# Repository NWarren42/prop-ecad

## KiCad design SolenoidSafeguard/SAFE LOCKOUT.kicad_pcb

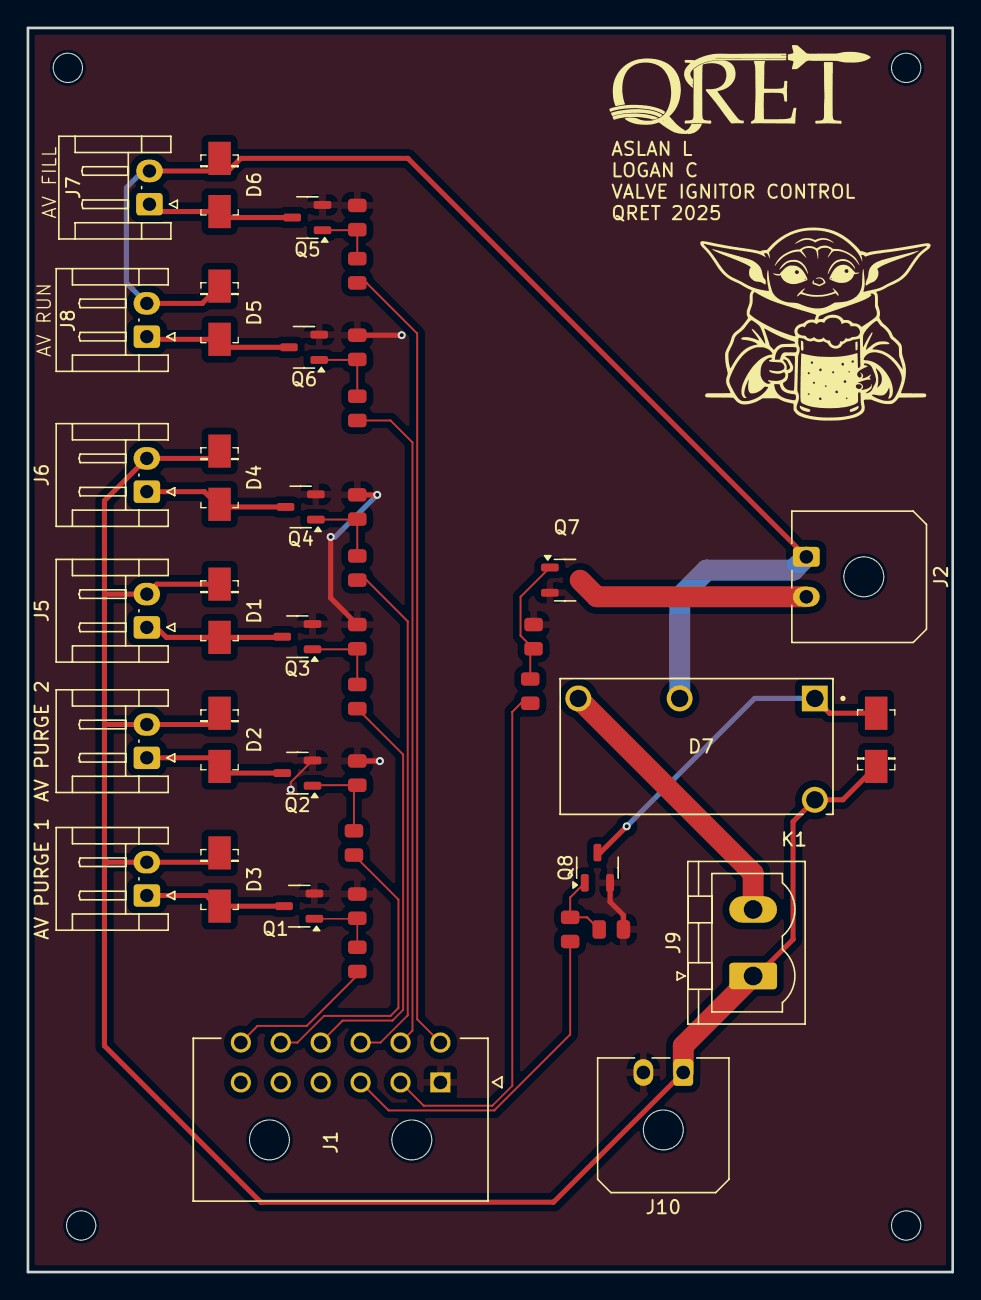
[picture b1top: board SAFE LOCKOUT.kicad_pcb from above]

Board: 2 copper layers, 69.5 x 93.5 mm, 42 parts (0 on the bottom side), 28 nets.

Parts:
AV PURGE 1, AV PURGE 2: Conn_01x02_Pin; JST_EH_S2B-EH_1x02_P2.50mm_Horizontal
D1, D2, D3, D4, D5, D6, D7: S1G; DO-214AC
J1: Conn_01x12_Pin; MOLEX_430451200
J2, J10: Conn_01x02_Pin; Molex_Micro-Fit_3.0_43650-0200_1x02_P3.00mm_Horizontal
J5, J6, J7, J8: Conn_01x02_Pin; JST_EH_S2B-EH_1x02_P2.50mm_Horizontal
J9: Conn_01x02_Pin; PhoenixContact_MSTBVA_2,5_2-G_1x02_P5.00mm_Vertical
K1: PR30-24V-450-1A; RELAY_PR30-24V-450-1A
Q1, Q2, Q3, Q4, Q5, Q6, Q7, Q8: BSS138; SOT-23-3
R1, R3, R5, R7, R9, R11, R13, R15: R100; R_0805
R2, R4, R6, R8, R10, R12, R16: 100KR; R_0805
R14: R100K; R_0805

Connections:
+24V: AV PURGE 1.2, AV PURGE 2.2, D1.K, D2.K, D3.K, D4.K, D7.K, J5.2, J6.2, J9.1, J10.1, K1.16
AV RUN CTL: J1.8, R11.1
AV FILL CTL: J1.7, R9.1
AV FILL VLV: D6.A, J7.1, Q5.3 (D)
AV RUN VLV: D5.A, J8.1, Q6.3 (D)
GND: J1.1, J10.2, Q1.2 (S), Q2.2 (S), Q3.2 (S), Q4.2 (S), Q5.2 (S), Q6.2 (S), Q7.2 (S), Q8.2 (S), R2.1, R4.1, R6.1, R8.1, R10.1, R12.1, R14.1, R16.1
IGNITOR 3A -: J2.2, Q7.3 (D)
IGNITOR CTL: J1.2, R13.1
unnamed: J9.2, K1.8
unnamed: Q1.1 (G), R1.2, R2.2
unnamed: Q2.1 (G), R3.2, R4.2
unnamed: Q3.1 (G), R5.2, R6.2
unnamed: Q4.1 (G), R7.2, R8.2
unnamed: Q5.1 (G), R9.2, R10.2
unnamed: Q6.1 (G), R11.2, R12.2
unnamed: Q7.1 (G), R13.2, R14.2
unnamed: D7.A, K1.1, Q8.3 (D)
unnamed: Q8.1 (G), R15.2, R16.2
RELAY SFEGRD CTL: J1.3, R15.1
SAFE POWER 24v: D5.K, D6.K, J2.1, J7.2, J8.2, K1.5
VLV 1: AV PURGE 1.1, D3.A, Q1.3 (D)
VLV 1 CTL: J1.12, R1.1
VLV 2: AV PURGE 2.1, D2.A, Q2.3 (D)
VLV 2 CTL: J1.11, R3.1
VLV 3: D1.A, J5.1, Q3.3 (D)
VLV 3 CTL: J1.10, R5.1
VLV 4: D4.A, J6.1, Q4.3 (D)
VLV 4 CTL: J1.9, R7.1

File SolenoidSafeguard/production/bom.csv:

Designator,Footprint,Quantity,Value,LCSC Part #
"D1, D2, D3, D4, D5, D6, D7",DO-214AC,7,S1G,S1G
J1,MOLEX_430451200,1,Conn_01x12_Pin,
"J10, J2",Molex_Micro-Fit_3.0_43650-0200_1x02_P3.00mm_Horizontal,2,Conn_01x02_Pin,
"J3, J4, J5, J6, J7, J8",JST_EH_S2B-EH_1x02_P2.50mm_Horizontal,6,Conn_01x02_Pin,
J9,"PhoenixContact_MSTBVA_2,5_2-G_1x02_P5.00mm_Vertical",1,Conn_01x02_Pin,
K1,RELAY_PR30-24V-450-1A,1,PR30-24V-450-1A,
"Q1, Q2, Q3, Q4, Q5, Q6, Q7, Q8",SOT-23-3,8,BSS138,BSS138
"R1, R11, R13, R15, R3, R5, R7, R9",R_0805,8,R100,
"R10, R12, R16, R2, R4, R6, R8",R_0805,7,100KR,
R14,R_0805,1,R100K,

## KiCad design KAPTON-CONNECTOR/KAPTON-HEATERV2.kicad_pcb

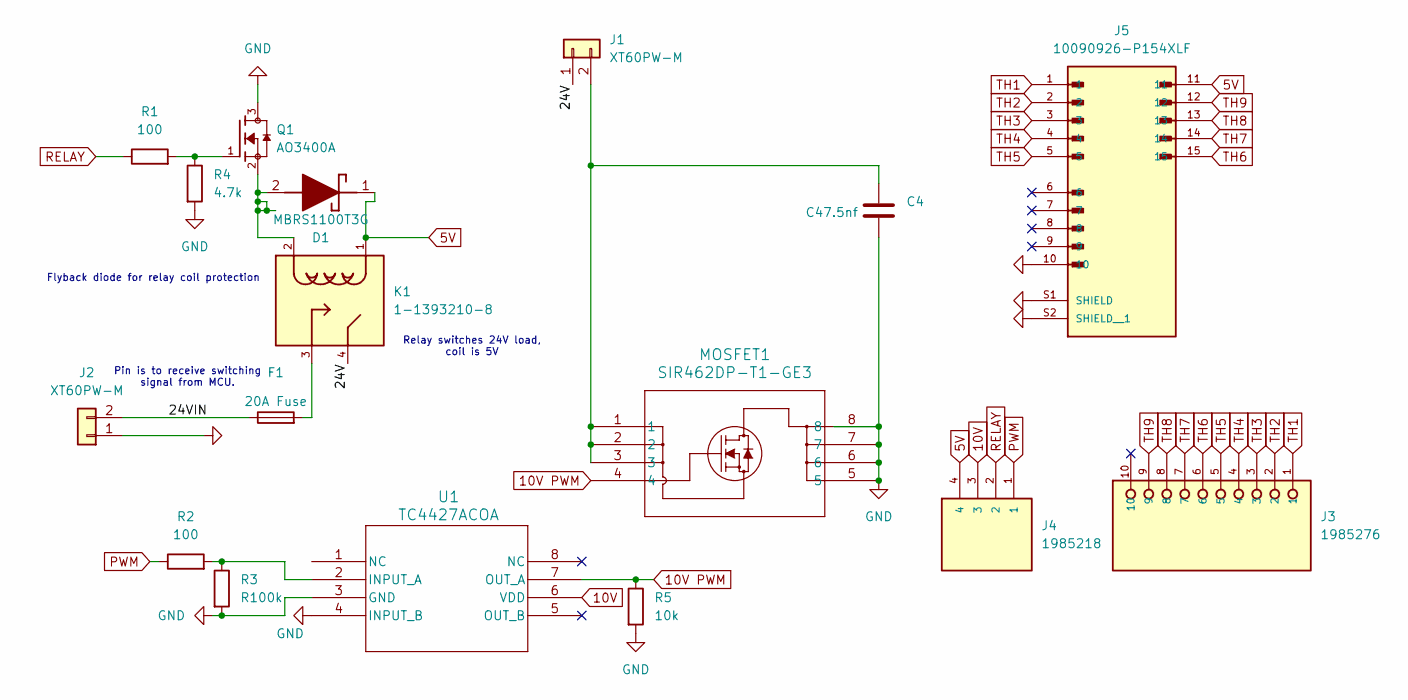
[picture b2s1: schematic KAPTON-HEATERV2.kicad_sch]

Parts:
C4: C47.5nf; C_0805_2012Metric
D1: MBRS1100T3G; DIOM5436X247N; Mouser Part Number 863-MBRS1100T3G
F1: 20A Fuse; FUSRR508W60L835T400H810
J1, J2: XT60PW-M; AMASS_XT60PW-M
J3: 1985276; PHOENIX_1985276
J4: 1985218; TE_1985218; PARTREV 29.03.2021
J5: 10090926-P154XLF; AMPHENOL_10090926-P154XLF; PARTREV H
K1: 1-1393210-8; RELAY_1-1393210-8; PARTREV 0815
MOSFET1: SIR462DP-T1-GE3; POWERPAK_SO-8_SINGLE_VIS
Q1: AO3400A; SOT95P280X125-3N; PARTREV L
R1, R2: 100; R_1206
R3: R100k; R_0805_2012Metric
R4: 4.7k; R_1206
R5: 10k; R_1206
U1: TC4427ACOA; SOIC8-N_MC_MCH

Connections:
5V: D1.1 (K), J4.4, J5.11, K1.1
10V: J4.3, U1.6 (VDD)
10V PWM: MOSFET1.4, R5.1, U1.7 (OUT_A)
/24V: J1.1, K1.4
/24VIN: F1.1, J2.2
GND: C4.1, J2.1, J5.10, J5.S1 (SHIELD), J5.S2 (SHIELD__1), MOSFET1.5, MOSFET1.6, MOSFET1.7, MOSFET1.8, Q1.3, R3.2, R4.2, R5.2, U1.3 (GND), U1.4 (INPUT_B)
unnamed: D1.2 (A), K1.2, Q1.2
unnamed: F1.2, K1.3
unnamed: C4.2, J1.2, MOSFET1.1, MOSFET1.2, MOSFET1.3
unnamed: Q1.1, R1.2, R4.1
unnamed: R2.2, R3.1, U1.2 (INPUT_A)
PWM: J4.1, R2.1
RELAY: J4.2, R1.1
TH1: J3.1, J5.1
TH2: J3.2, J5.2
TH3: J3.3, J5.3
TH4: J3.4, J5.4
TH5: J3.5, J5.5
TH6: J3.6, J5.15
TH7: J3.7, J5.14
TH8: J3.8, J5.13
TH9: J3.9, J5.12

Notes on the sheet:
Relay switches 24V load, coil is 5V
Flyback diode for relay coil protection
Pin is to receive switching signal from MCU.

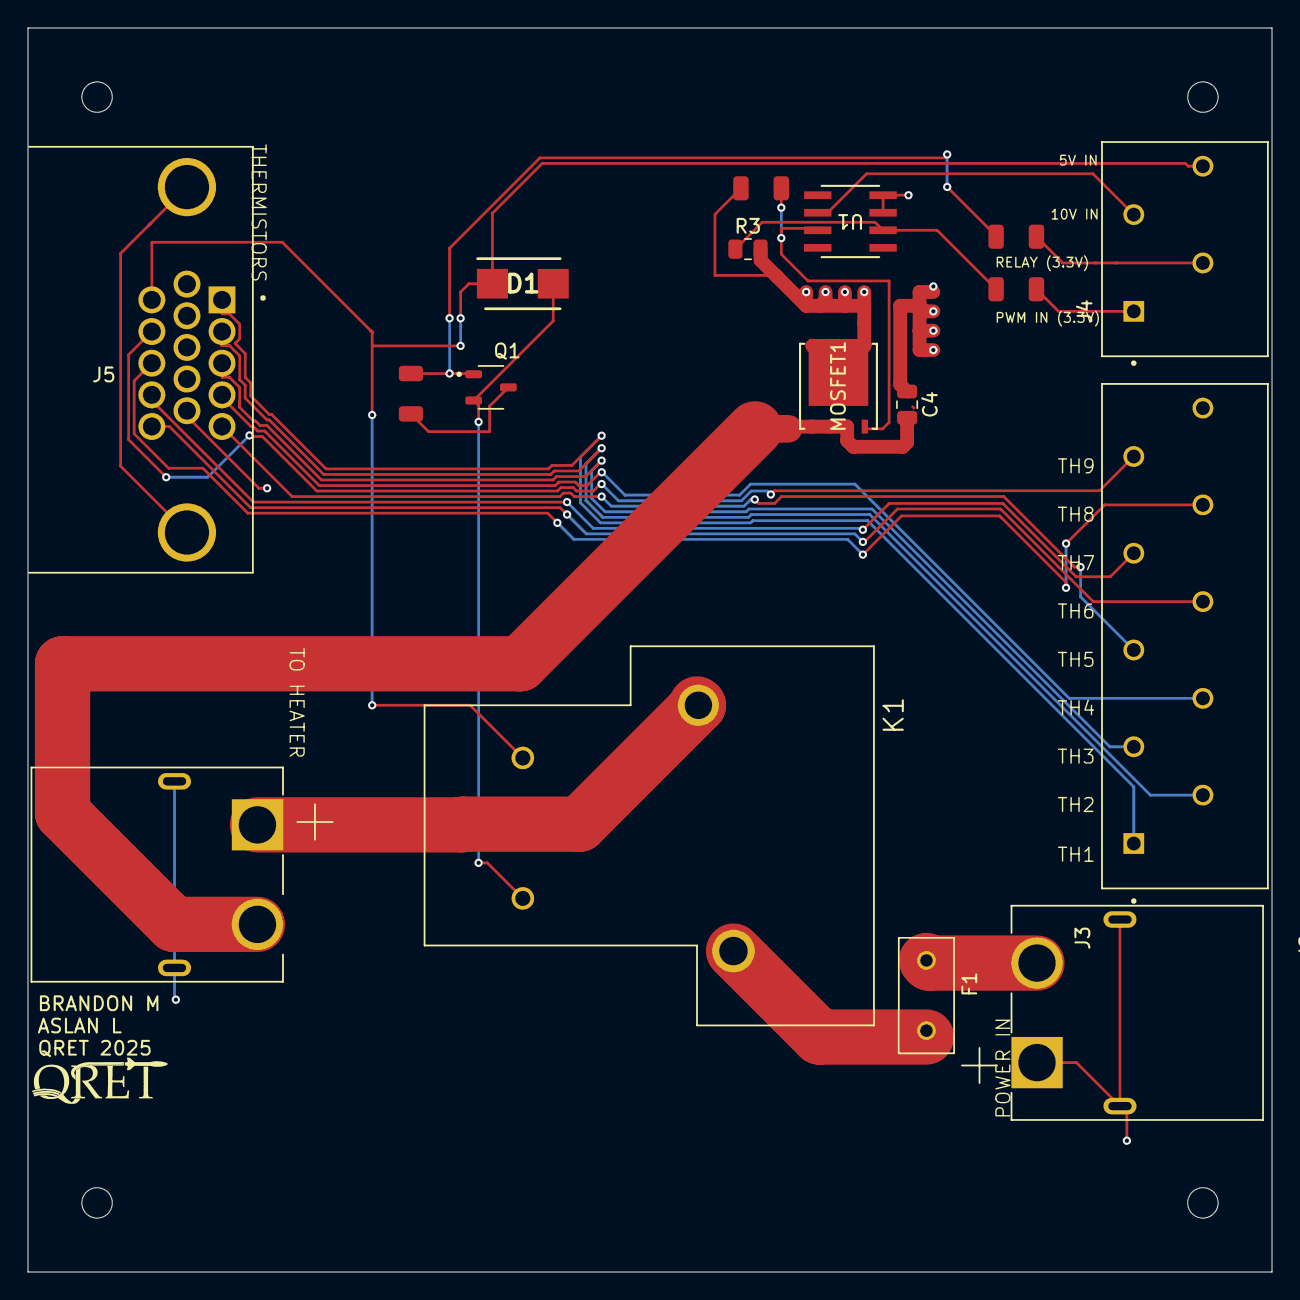
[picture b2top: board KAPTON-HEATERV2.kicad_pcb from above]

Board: 2 copper layers, 90.0 x 90.0 mm, 17 parts (0 on the bottom side), 22 nets.

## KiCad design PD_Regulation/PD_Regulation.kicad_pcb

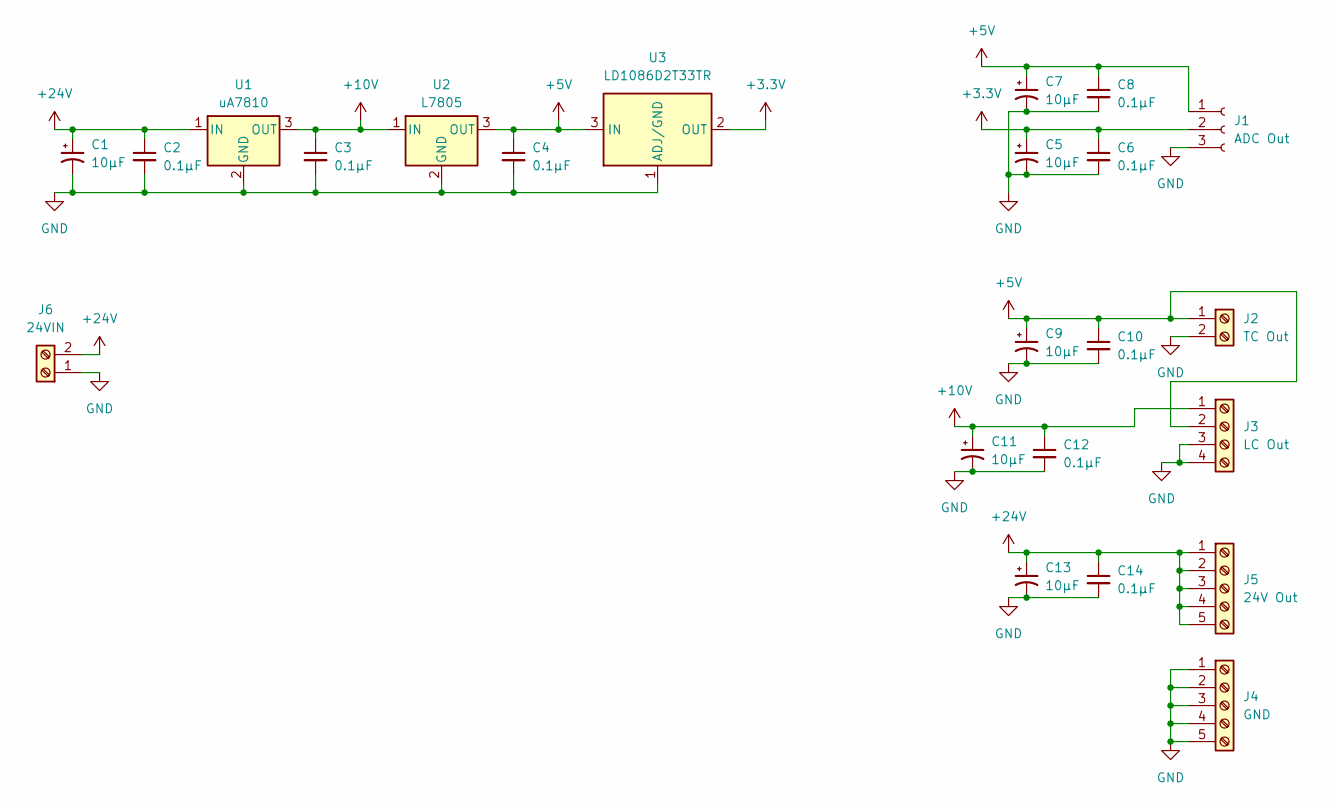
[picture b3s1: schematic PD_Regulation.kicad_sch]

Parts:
C1, C5, C7, C9, C11, C13: 10μF; CP_Radial_D5.0mm_P2.00mm
C2, C3, C4, C6, C8, C10, C12, C14: 0.1μF; C_Disc_D4.7mm_W2.5mm_P5.00mm
J1: ADC Out; JST_XH_B3B-XH-A_1x03_P2.50mm_Vertical
J2: TC Out; TerminalBlock_Xinya_XY308-2.54-2P_1x02_P2.54mm_Horizontal
J3: LC Out; TerminalBlock_Xinya_XY308-2.54-4P_1x04_P2.54mm_Horizontal
J4: GND; TerminalBlock_Xinya_XY308-2.54-5P_1x05_P2.54mm_Horizontal
J5: 24V Out; TerminalBlock_Xinya_XY308-2.54-5P_1x05_P2.54mm_Horizontal
J6: 24VIN; TerminalBlock_Xinya_XY308-2.54-2P_1x02_P2.54mm_Horizontal
U1: uA7810; TO-263-3_TabPin2
U2: L7805; TO-263-2
U3: LD1086D2T33TR; TO-263-2

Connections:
+3.3V: C5.1, C6.1, J1.2, U3.2 (OUT)
+5V: C4.1, C7.1, C8.1, C9.1, C10.1, J1.1, J2.1, J3.2, U2.3 (OUT), U3.3 (IN)
+10V: C3.1, C11.1, C12.1, J3.1, U1.3 (OUT), U2.1 (IN)
+24V: C1.1, C2.1, C13.1, C14.1, J5.1, J5.2, J5.3, J5.4, J5.5, J6.2, U1.1 (IN)
GND: C1.2, C2.2, C3.2, C4.2, C5.2, C6.2, C7.2, C8.2, C9.2, C10.2, C11.2, C12.2, C13.2, C14.2, J1.3, J2.2, J3.3, J3.4, J4.1, J4.2, J4.3, J4.4, J4.5, J6.1, U1.2 (GND), U2.2 (GND), U3.1 (ADJ/GND)

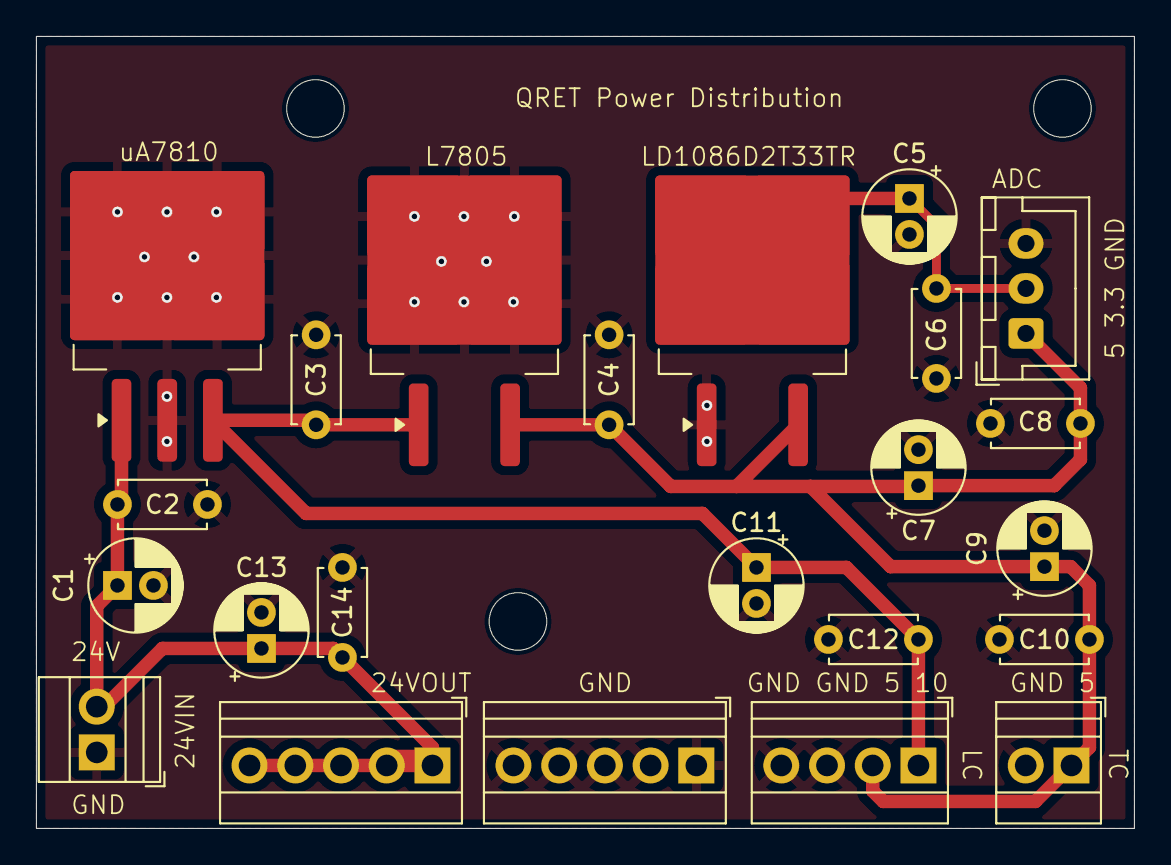
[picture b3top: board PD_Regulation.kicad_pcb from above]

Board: 2 copper layers, 61.0 x 44.0 mm, 26 parts (0 on the bottom side), 5 nets.

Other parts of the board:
H1, H1#2, H1#3: MountingHole; MountingHole_3.2mm_M3_DIN965

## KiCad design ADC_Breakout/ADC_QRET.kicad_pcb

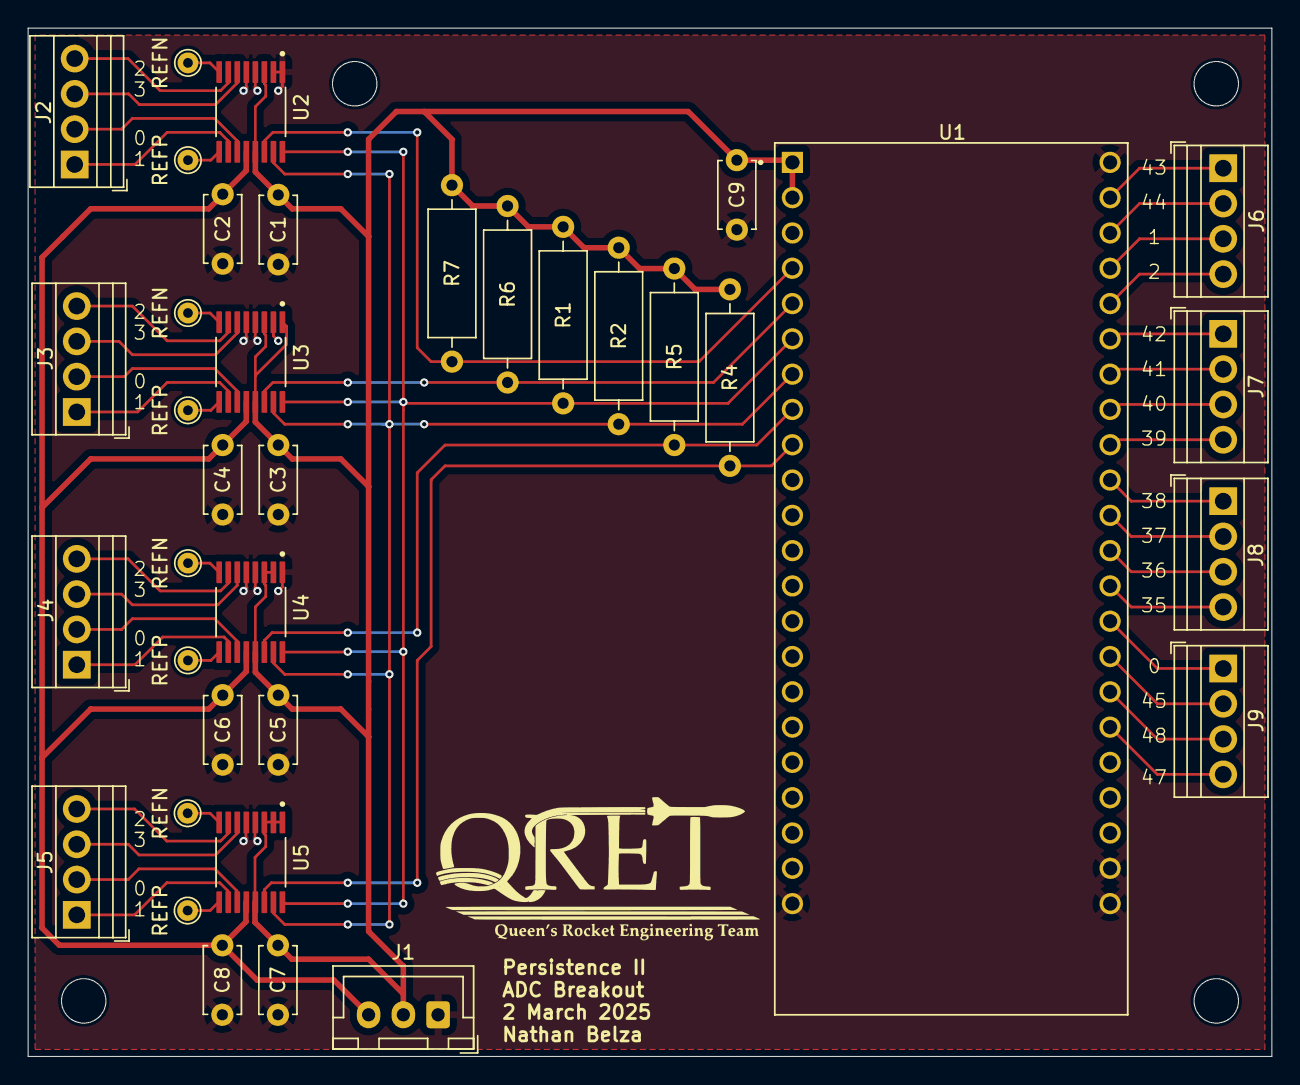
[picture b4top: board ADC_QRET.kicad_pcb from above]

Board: 2 copper layers, 89.5 x 74.0 mm, 41 parts (0 on the bottom side), 49 nets.

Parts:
C1, C2, C3, C4, C5, C6, C7, C8, C9: 0.1μF; C_Disc_D4.7mm_W2.5mm_P5.00mm
H1, H1#2, H1#3, H1#4: MountingHole; MountingHole_3.2mm_M3_DIN965
J1: Screw_Terminal_01x03; JST_XH_B3B-XH-A_1x03_P2.50mm_Vertical
J2, J3, J4, J5, J6, J7, J8, J9: Screw_Terminal_01x04; TerminalBlock_Xinya_XY308-2.54-4P_1x04_P2.54mm_Horizontal
R1, R2, R4, R5, R6, R7: 4.7kΩ; R_Axial_DIN0309_L9.0mm_D3.2mm_P12.70mm_Horizontal
REFN: TestPoint_Small; TestPoint_THTPad_D1.5mm_Drill0.7mm
REFN#2, REFN#3, REFN#4: TestPoint_Small; TestPoint_THTPad_D1.5mm_Drill0.7mm
REFP: TestPoint_Small; TestPoint_THTPad_D1.5mm_Drill0.7mm
REFP#2, REFP#3, REFP#4: TestPoint_Small; TestPoint_THTPad_D1.5mm_Drill0.7mm
U1: ESP32-S3-DEVKITC-1-N8R2; XCVR_ESP32-S3-DEVKITC-1-N8R2
U2, U3, U4, U5: SOP65P640X120-16N

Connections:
+3.3V: C1.1, C3.1, C5.1, C7.1, C9.2, J1.2, R1.1, R2.1, R4.1, R5.1, R6.1, R7.1, U1.J1_1 (3V3), U1.J1_2 (3V3), U2.3 (RESET), U2.13 (DVDD), U3.1 (A0), U3.3 (RESET), U3.13 (DVDD), U4.2 (A1), U4.3 (RESET), U4.13 (DVDD), U5.1 (A0), U5.2 (A1), U5.3 (RESET), U5.13 (DVDD)
+5V: C2.1, C4.1, C6.1, C8.1, J1.3, U2.12 (AVDD), U3.12 (AVDD), U4.12 (AVDD), U5.12 (AVDD)
GND: C1.2, C2.2, C3.2, C4.2, C5.2, C6.2, C7.2, C8.2, C9.1, J1.1, U1.J1_22 (GND), U1.J3_1 (GND), U1.J3_21 (GND), U1.J3_22 (GND), U2.1 (A0), U2.2 (A1), U2.4 (DGND), U2.5 (AVSS), U3.2 (A1), U3.4 (DGND), U3.5 (AVSS), U4.1 (A0), U4.4 (DGND), U4.5 (AVSS), U5.4 (DGND), U5.5 (AVSS)
unnamed: J2.1, U2.11 (AIN0)
unnamed: J2.2, U2.10 (AIN1)
unnamed: J2.3, U2.7 (AIN2)
unnamed: J2.4, U2.6 (AIN3)
unnamed: J3.1, U3.11 (AIN0)
unnamed: J3.2, U3.10 (AIN1)
unnamed: J3.3, U3.7 (AIN2)
unnamed: J3.4, U3.6 (AIN3)
unnamed: J4.1, U4.11 (AIN0)
unnamed: J4.2, U4.10 (AIN1)
unnamed: J4.3, U4.7 (AIN2)
unnamed: J4.4, U4.6 (AIN3)
unnamed: J5.1, U5.11 (AIN0)
unnamed: J5.2, U5.10 (AIN1)
unnamed: J5.3, U5.7 (AIN2)
unnamed: J5.4, U5.6 (AIN3)
unnamed: J6.1, U1.J3_2 (U0TXD/GPIO43)
unnamed: J6.2, U1.J3_3 (U0RXD/GPIO44)
unnamed: J6.3, U1.J3_4 (GPIO1)
unnamed: J6.4, U1.J3_5 (GPIO2)
unnamed: J7.1, U1.J3_9 (MTCK/GPIO39)
unnamed: J7.2, U1.J3_8 (MTDO/GPIO40)
unnamed: J7.3, U1.J3_7 (MTDI/GPIO41)
unnamed: J7.4, U1.J3_6 (MTMS/GPIO42)
unnamed: J8.1, U1.J3_13 (GPIO35)
unnamed: J8.2, U1.J3_12 (GPIO36)
unnamed: J8.3, U1.J3_11 (GPIO37)
unnamed: J8.4, U1.J3_10 (GPIO38)
unnamed: J9.1, U1.J3_14 (GPIO0)
unnamed: J9.2, U1.J3_15 (GPIO45)
unnamed: J9.3, U1.J3_16 (GPIO48)
unnamed: J9.4, U1.J3_17 (GPIO47)
unnamed: R7.2, U1.J1_4 (GPIO4), U2.14 (DRDY)
unnamed: R6.2, U1.J1_5 (GPIO5), U3.14 (DRDY)
unnamed: R1.2, U1.J1_6 (GPIO6), U2.16 (SCL), U3.16 (SCL), U4.16 (SCL), U5.16 (SCL)
unnamed: R2.2, U1.J1_7 (GPIO7), U2.15 (SDA), U3.15 (SDA), U4.15 (SDA), U5.15 (SDA)
unnamed: R5.2, U1.J1_8 (GPIO15), U4.14 (DRDY)
unnamed: R4.2, U1.J1_9 (GPIO16), U5.14 (DRDY)
unnamed: REFN#2.1, U2.8 (REFN)
unnamed: REFP#3.1, U2.9 (REFP)
unnamed: REFN#4.1, U3.8 (REFN)
unnamed: REFP.1, U3.9 (REFP)
unnamed: REFN#3.1, U4.8 (REFN)
unnamed: REFP#4.1, U4.9 (REFP)
unnamed: REFN.1, U5.8 (REFN)
unnamed: REFP#2.1, U5.9 (REFP)

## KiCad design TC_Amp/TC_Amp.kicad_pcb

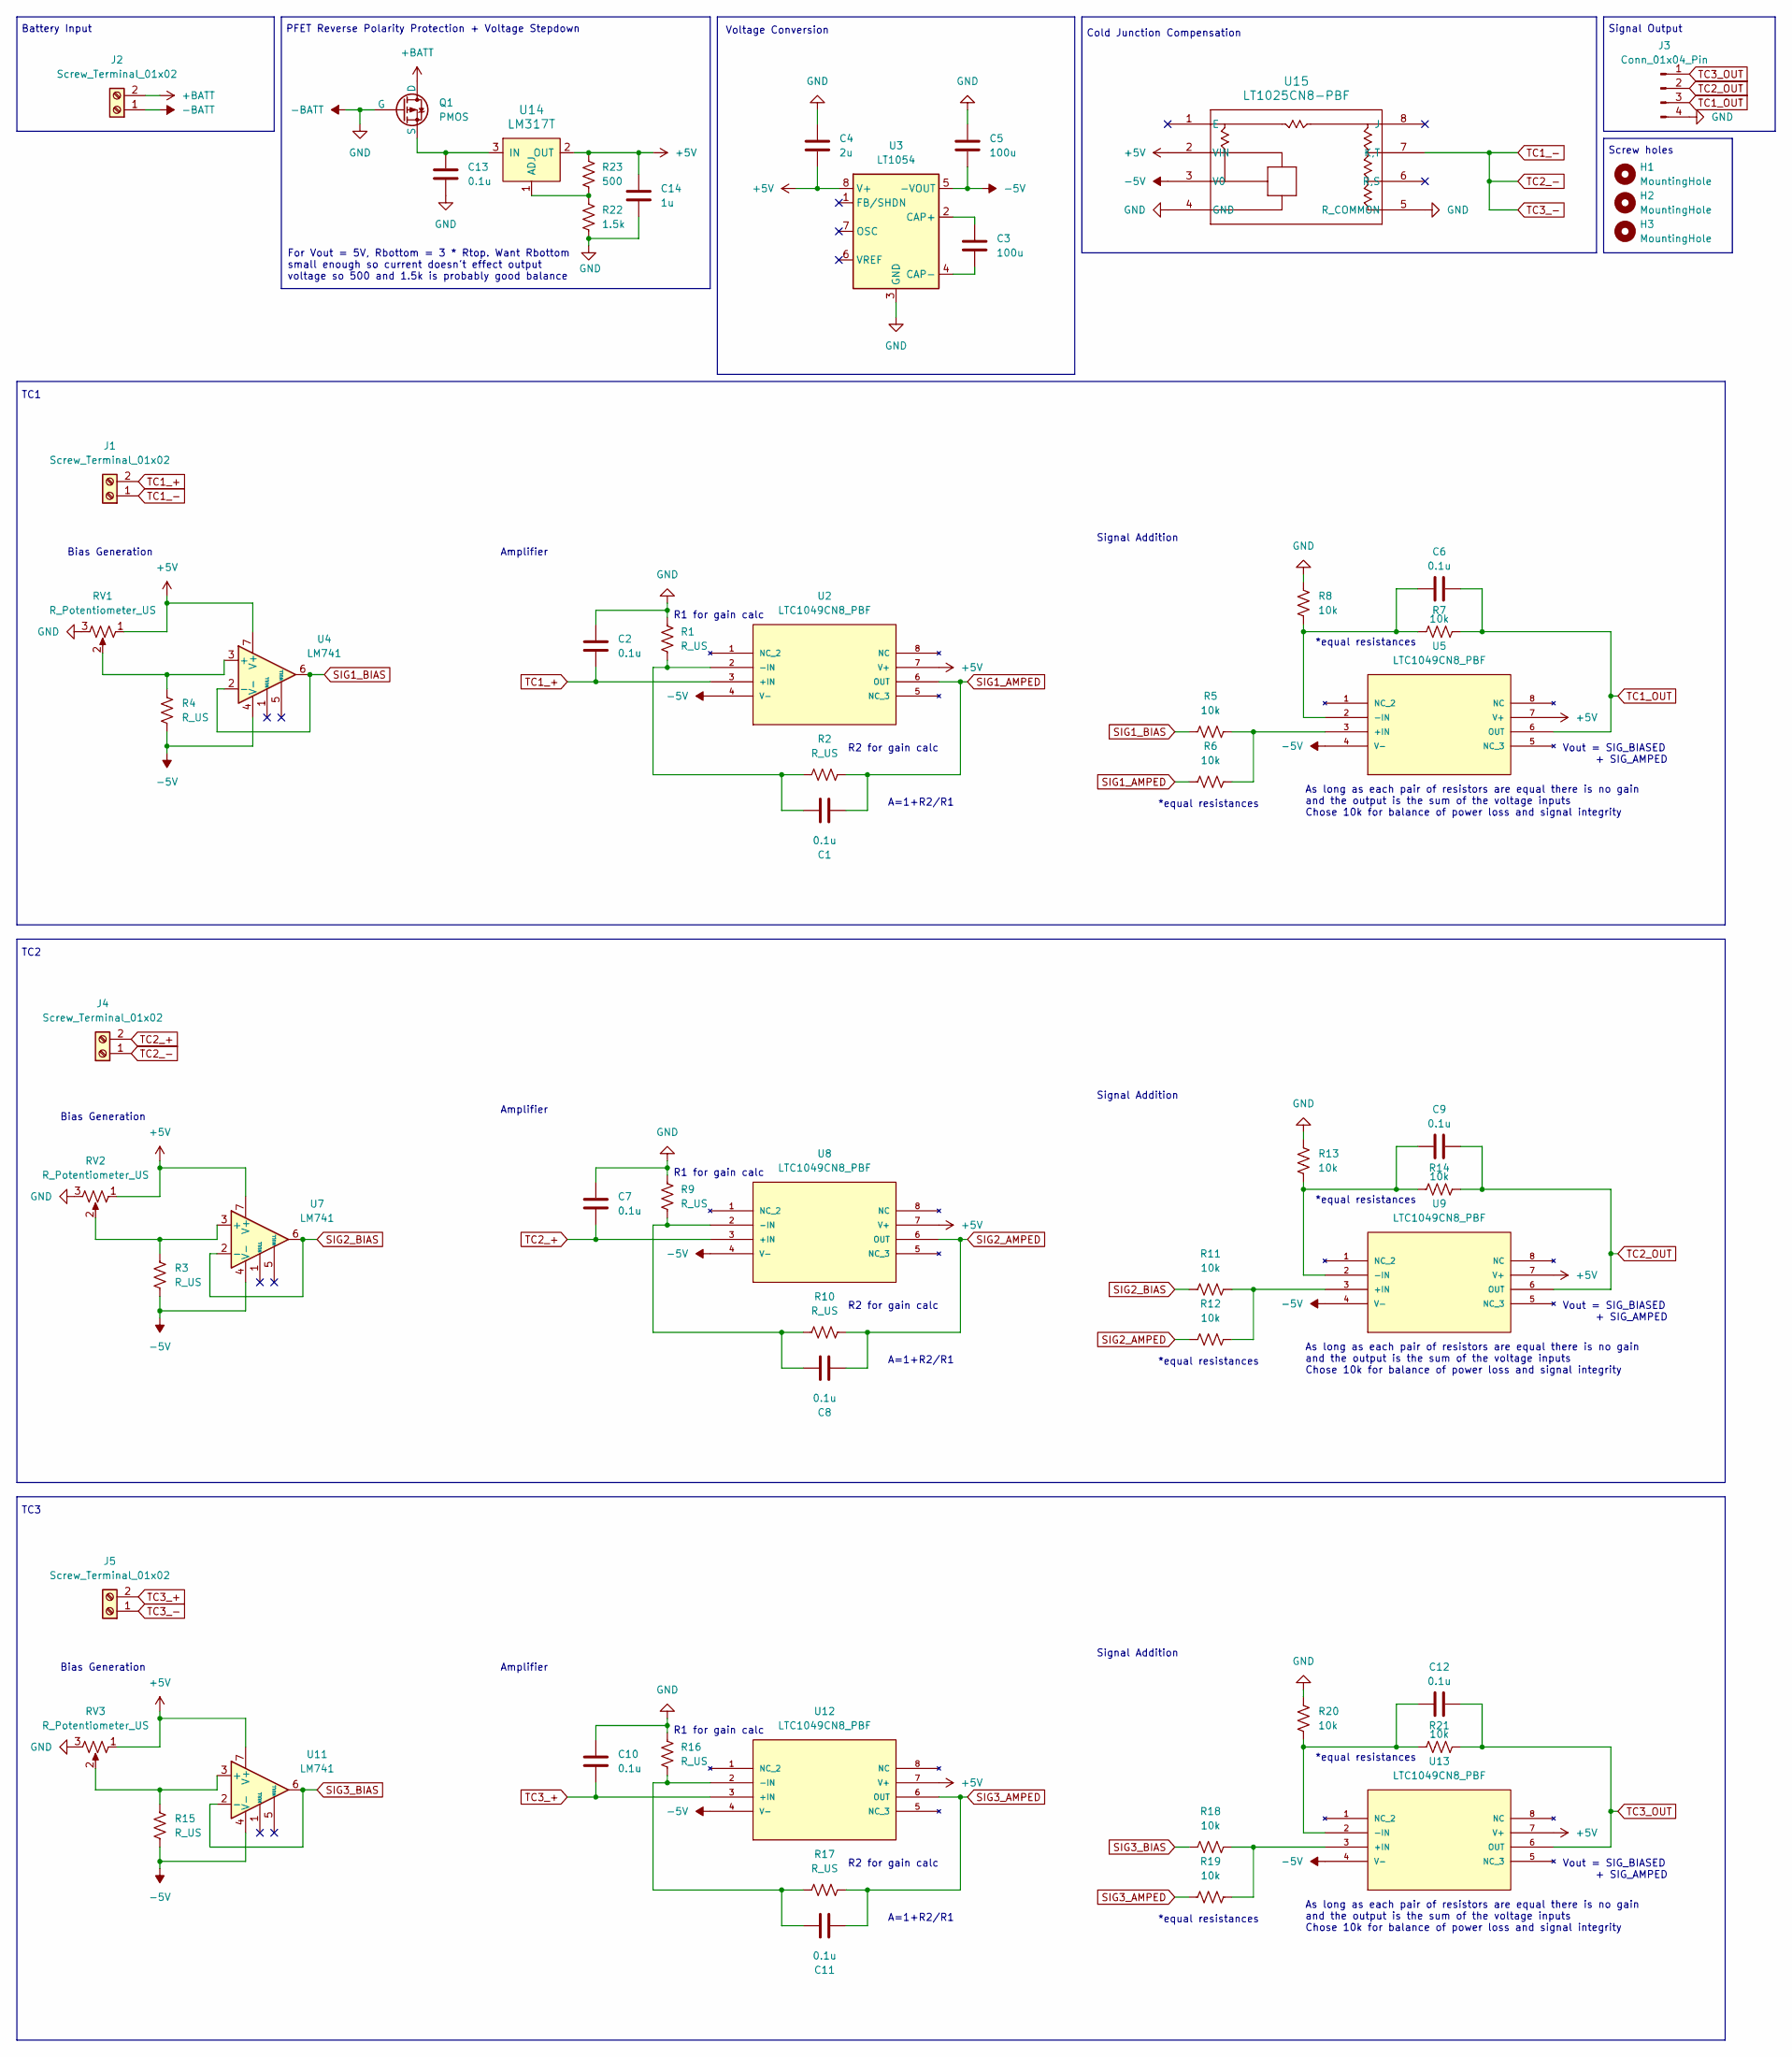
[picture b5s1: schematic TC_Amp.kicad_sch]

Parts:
C1, C2, C6, C7, C8, C9, C10, C11, C12, C13: 0.1u; C_Radial_D5.0mm_H5.0mm_P2.00mm
C3, C5: 100u; C_Radial_D5.0mm_H5.0mm_P2.00mm
C4: 2u; C_Radial_D5.0mm_H5.0mm_P2.00mm
C14: 1u; C_Radial_D5.0mm_H5.0mm_P2.00mm
H1, H2, H3: MountingHole; MountingHole_3.2mm_M3_DIN965
J1, J4, J5: Screw_Terminal_01x02; TC_SOCKET
J2: Screw_Terminal_01x02; TerminalBlock_bornier-2_P5.08mm
J3: Conn_01x04_Pin; PinHeader_1x04_P2.54mm_Vertical
Q1: PMOS; PFET_VERT
R1, R2, R3, R4, R9, R10, R15, R16, R17: R_US; R_Axial_DIN0207_L6.3mm_D2.5mm_P10.16mm_Horizontal
R5, R6, R7, R8, R11, R12, R13, R14, R18, R19, R20, R21: 10k; R_Axial_DIN0207_L6.3mm_D2.5mm_P10.16mm_Horizontal
R22: 1.5k; R_Axial_DIN0207_L6.3mm_D2.5mm_P10.16mm_Horizontal
R23: 500; R_Axial_DIN0207_L6.3mm_D2.5mm_P10.16mm_Horizontal
RV1, RV2, RV3: R_Potentiometer_US; Potentiometer_Bourns_3386W_Horizontal
U2, U5, U8, U9, U12, U13: LTC1049CN8_PBF; PDIP-8_N; MANUFACTURER_PART_NUMBER ltc1049cn8
U3: LT1054; DIP794W45P254L959H508Q8
U4, U7, U11: LM741; J08A_TEX
U14: LM317T; TO-220-3; MPN LM317T; Digi-Key_PN 497-1575-5-ND
U15: LT1025CN8-PBF; PDIP8_LT1025CN8-PBF_ADI

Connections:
+5V: C4.2, C14.1, R23.1, RV1.1, RV2.1, RV3.1, U2.7 (V+), U3.8 (V+), U4.7 (V+), U5.7 (V+), U7.7 (V+), U8.7 (V+), U9.7 (V+), U11.7 (V+), U12.7 (V+), U13.7 (V+), U14.2 (OUT), U15.2 (VIN)
+BATT: J2.2, Q1.1 (D)
-5V: C5.2, R3.1, R4.1, R15.1, U2.4 (V-), U3.5 (-VOUT), U4.4 (V-), U5.4 (V-), U7.4 (V-), U8.4 (V-), U9.4 (V-), U11.4 (V-), U12.4 (V-), U13.4 (V-), U15.3 (V0)
-BATT: C2.1, C4.1, C5.1, C7.1, C10.1, C13.2, C14.2, J2.1, J3.4, Q1.2 (G), R1.1, R8.2, R9.1, R13.2, R16.1, R20.2, R22.2, RV1.3, RV2.3, RV3.3, U3.3 (GND), U15.4 (GND), U15.5 (R_COMMON)
unnamed: C13.1, Q1.3 (S), U14.3 (IN)
unnamed: C1.1, R1.2, R2.1, U2.2 (-IN)
unnamed: C3.1, U3.2 (CAP+)
unnamed: C3.2, U3.4 (CAP-)
unnamed: R4.2, RV1.2, U4.3 (+)
unnamed: R5.2, R6.2, U5.3 (+IN)
unnamed: C6.2, R7.1, R8.1, U5.2 (-IN)
unnamed: R3.2, RV2.2, U7.3 (+)
unnamed: C8.1, R9.2, R10.1, U8.2 (-IN)
unnamed: R11.2, R12.2, U9.3 (+IN)
unnamed: C9.2, R13.1, R14.1, U9.2 (-IN)
unnamed: R15.2, RV3.2, U11.3 (+)
unnamed: C11.1, R16.2, R17.1, U12.2 (-IN)
unnamed: R18.2, R19.2, U13.3 (+IN)
unnamed: C12.2, R20.1, R21.1, U13.2 (-IN)
unnamed: R22.1, R23.2, U14.1 (ADJ)
SIG1_AMPED: C1.2, R2.2, R6.1, U2.6 (OUT)
SIG1_BIAS: R5.1, U4.2 (-), U4.6
SIG2_AMPED: C8.2, R10.2, R12.1, U8.6 (OUT)
SIG2_BIAS: R11.1, U7.2 (-), U7.6
SIG3_AMPED: C11.2, R17.2, R19.1, U12.6 (OUT)
SIG3_BIAS: R18.1, U11.2 (-), U11.6
TC1_+: C2.2, J1.2, U2.3 (+IN)
TC1_-: J1.1, J4.1, J5.1, U15.7 (K,T)
TC1_OUT: C6.1, J3.3, R7.2, U5.6 (OUT)
TC2_+: C7.2, J4.2, U8.3 (+IN)
TC2_OUT: C9.1, J3.2, R14.2, U9.6 (OUT)
TC3_+: C10.2, J5.2, U12.3 (+IN)
TC3_OUT: C12.1, J3.1, R21.2, U13.6 (OUT)

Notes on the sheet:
A=1+R2/R1
R1 for gain calc
*equal resistances
As long as each pair of resistors are equal there is no gain and the output is the sum of the voltage inputs Chose 10k for balance of power loss and signal integrity
Vout = SIG_BIASED + SIG_AMPED
Voltage Conversion
R2 for gain calc
For Vout = 5V, Rbottom = 3 * Rtop. Want Rbottom small enough so current doesn't effect output voltage so 500 and 1.5k is probably good balance
Bias Generation
Battery Input
Signal Output
Cold Junction Compensation
PFET Reverse Polarity Protection + Voltage Stepdown
TC3
Amplifier
TC1
Screw holes
Signal Addition
TC2

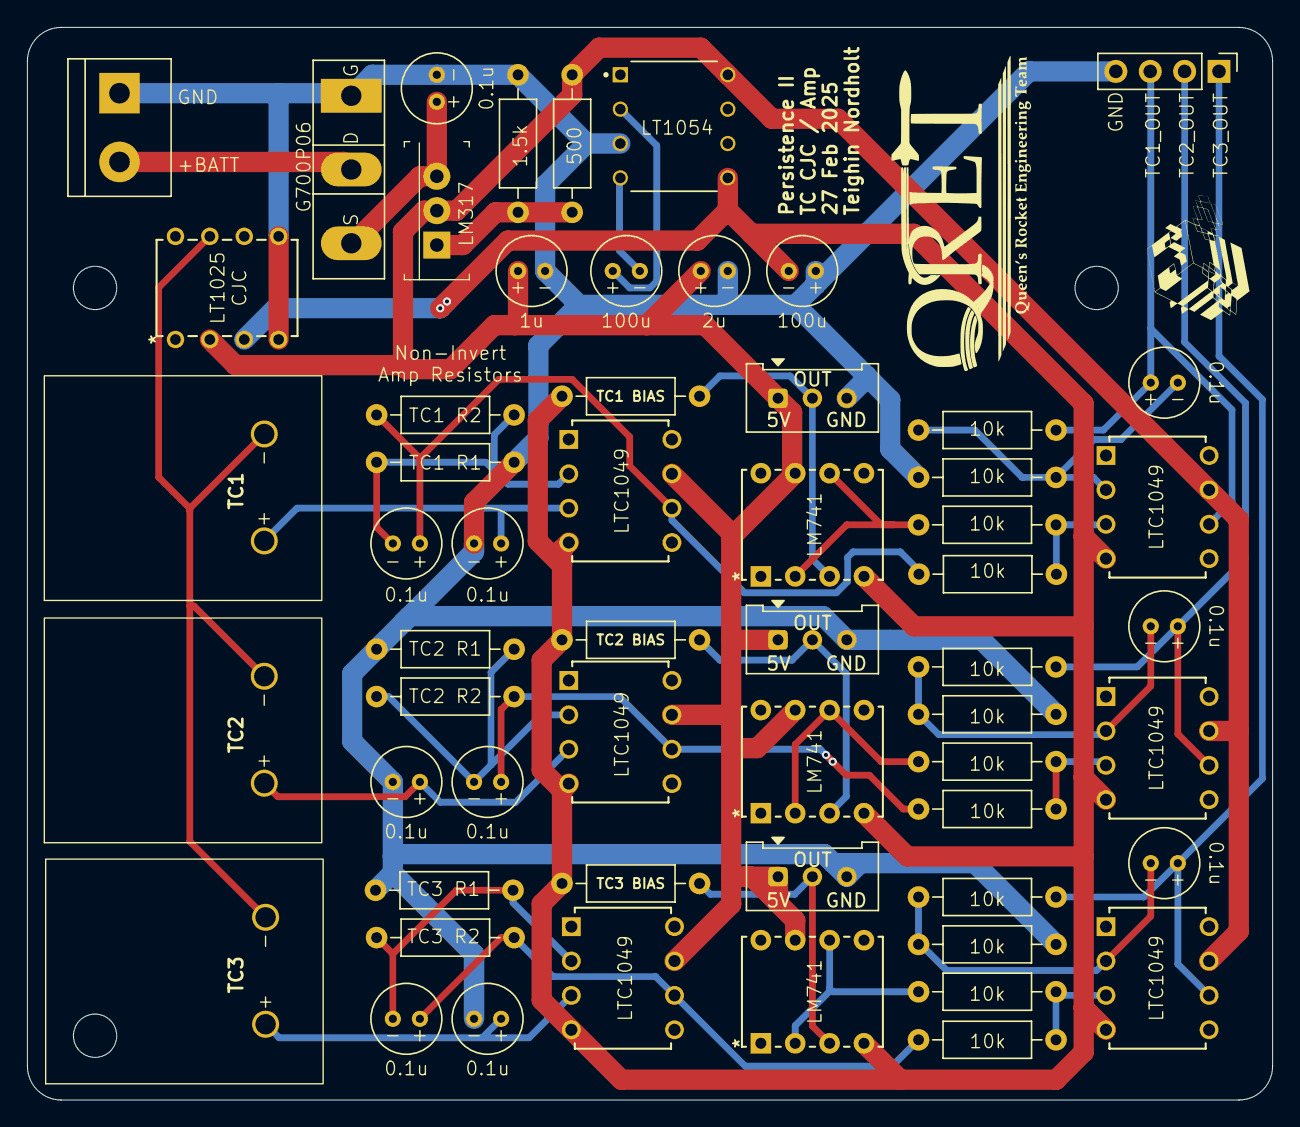
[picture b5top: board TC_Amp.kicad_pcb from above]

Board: 2 copper layers, 92.0 x 79.2 mm, 61 parts (0 on the bottom side), 33 nets.

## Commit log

2025-02-07 Add first thermocouple amp files
2025-02-07 seperated screw terminals
2025-02-09 added charge pump spice sim
2025-02-09 added new footprints
2025-02-09 updated schematic and added three tcs
2025-02-10 added voltage regulation sim
2025-02-10 added custom PFET footprint for g700p06
2025-02-10 changed to 5v regulation
2025-02-10 added board
2025-02-10 added gitignore
2025-02-10 misc files
2025-02-10 change to common cjc
2025-02-10 updated layout before traces
2025-02-10 finished prelim traces
2025-02-12 added silkscreen
2025-02-12 removed backups
2025-02-28 rounded etch corners and added m3 holes
2025-03-02 Initial ADC Breakout Commit
2025-03-02 nathan first commit
2025-03-02 Updated silkscreen
2025-03-05 Added ESP32 IO Terminals
2025-03-07 Added standoff holes
2025-03-09 Initial commit for power delivery board
2025-03-09 Completed PCB for PD board
2025-03-09 Added vias
2025-04-15 Arduino script for testing
2025-04-16 updated amplifier values
2025-04-16 updated schematic with physical changes
    removed linear regulator to mandate 5v input, added 10k resistor to R- of CJC
2025-06-05 added KAPTON_CONNECTOR
2025-07-15 Fuck u aslan
2025-07-21 updated safeguard board

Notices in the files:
parts and their libraries:
COPYRIGHT: Copyright C 2016 Accelerated Designs. All rights reserved
